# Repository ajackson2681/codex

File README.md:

# Codex

The Codex is an attempt at an open-source, distraction-free writing device inspired somewhat by the AlphaSmart Neo (at least the display was). The Codex pairs a 40x4 character LCD with USB HID keyboard support, and SD card storage. For a more in-depth summary/breakdown, you can visit the page I have on my website: [Codex Web Page](https://adamjackson.dev/codex.html).

---

## Project Status

Codex is under active development. Current state:

**Working:**
- [x] LCD driver
  - Originally used a derivation of the Arduino LiquidCrystal library (noted below under [Libraries Used](#libraries-used) and [Acknowledgements](#acknowledgments)). I have since written a custom one from the ground up specific for this project.
- [x] USB HID keyboard input via TinyUSB
- [x] Gap buffer with insert/delete/backspace
- [x] Character, word, line, frame, and document navigation
- [x] Frame buffer rendering (LCD stays in sync with cursor position)
- [x] SD card read/write (FatFs via [no-OS-FatFS-SD-SPI-RPi-Pico](https://github.com/carlk3/no-OS-FatFS-SD-SPI-RPi-Pico))
- [x] Document save/load
- [x] File selection on boot
- [x] Tab handling (inserted as two spaces)
- [x] Home/End at line, frame, and document scope
- [x] Card detect

**In progress / planned:**
- [ ] Keyboard shortcut finalization
- [ ] Save new document/give file name
- [ ] PWM backlight brightness control (potentiometer on one of the analog pins + transistor)
- [ ] Rev 2+ PCB: LiPo + boost converter, switchable external/battery power input, finalized sockets for ribbon cables/harnesses
- [ ] Final Enclosure (currently a wedge shape)
- [ ] Documentation: build guide, BOM, update procedure, etc.

**Maybes**
- [ ] Ability to change file after startup

**Explicitly out of scope (for now):**
- Text selection / clipboard
- Undo/redo
- Rich text or formatting of any kind

---

## Hardware

### Bill of Materials (high level)

| Component | Notes |
|---|---|
| Raspberry Pi Pico (RP2040) | Mounted via socket currently, likely castellated edge pads on the final PCB |
| 40x4 ST7066U character LCD | Dual controller (EN1/EN2), 4-bit mode |
| USB OTG converter | USB port for keyboard |
| SD card socket | SPI mode |
| Slide potentiometers (x2) | Contrast (to LCD V0) and brightness (to analog GPIO) |
| BC547 NPN transistor | PWM backlight switching |
| TP61090 boost converter | LiPo → 5V (Rev 2+) |
| MCP73871 charge controller | LiPo charge circuit (Rev 2+) |
| L7805 linear regulator | Bench/external power path (Rev0-Rev2, won't be on Rev3) |
| SPDT switch | Selects external 5V vs. LiPo/boost power source (Rev2 only), acts as power switch (Rev0 & Rev1) |
| LiPo cell | (Rev 2+) |

### PCB Revisions

| Rev | Purpose | Status |
|---|---|---|
| **Breadboard** | Initial validation: LCD, USB host, SD card | Done | 
| **Rev 0** | First PCB, puts the breadboard on a dedicated PCB, adds a power switch, adds filtering capacitors | Done |
| **Rev 1** | Fixes mistakes from Rev0. Sill uses socketed footprints for SD card and Pico. Adds breakout pins for contrast/brightness potentiometers, adds PWM backlight transistor. | Validating |
| **Rev 2** | Dedicated SD card slot, finalized sockets for IDC, potentiometers, and LED power. Pico footprint will allow sockets _or_ solder directly via castellated holes. 5v linear regulator will remain, with an optional switch for swapping to using a 5v direct power source (planned as a Powerboost 1000 module). | Designing |
| **Rev 3** | Removal of 5v linear regulator. Move to all SMD components for assembly by fab house. | Planned |
| **???** | Anything beyond Rev3 will only happen if I make dumb mistakes (and I probably will).

## Firmware

Built with the **Raspberry Pi Pico SDK**

### Libraries used

- Originally used a derivation of [LiquidCrystal440](https://github.com/jurs/liquidcrystal440), which is in turn a derivation of the [Original Arduino Library](https://github.com/arduino-libraries/LiquidCrystal).
  - Now uses a driver that is purpose-written for this device 
- **TinyUSB** - USB HID host
- **no-OS-FatFS-SD-SPI-RPi-Pico** - SD card / FAT filesystem (submodule)

### Recovery

If a firmware update fails or the device won't boot, hold **BOOTSEL** while connecting the Pico to a computer via USB. It will appear as a USB mass storage device. Then drag and drop a known-good `.uf2` to restore it. This is a hardware bootloader built into the RP2040 and cannot be bricked by firmware alone.

---

## Enclosure

Designed in FreeCAD. It has a sort of wedge factor with the 40x4 LCD forming most of the angled top face. Slide potentiometers for brightness and contrast are mounted on the front, with the the keyboard USB port and SD card slot to the right of those. FCStd files are located `3dmodels/` (I'm just committing the whole blob since I don't really know a better way to do it for freecad files in git).

---

## Keyboard Compatibility

The Codex _should_ work with any standard USB HID keyboard, both wired or via a wireless USB dongle. The Codex does **not** support bluetooth keyboards.

### Recommended

For a compact keyboard, a 65% or 75% layout is recommended for dedicated Home/End/Page Up/Page Down/Arrow keys without needing Fn combinations. Otherwise, pretty much whatever you're most comfortable with. I use an Epomaker TH80SE, which is a 75% keyboard. However, that doesn't have a dedicated "End" key (it's FN+PgDown). Something like the [Epomaker x Aula F65](https://epomaker.com/products/epomaker-aula-f65) or [Epomaker x Aula F75](https://epomaker.com/products/epomaker-aula-f75) could maybe be good choices that include all the buttons.

---

## Keyboard Shortcuts (WIP)

| Shortcut | Primary Action | Secondary Action
|---|---|---|
| Arrow keys | Move cursor (character / line) | |
| Ctrl + ←/→ | Move by word | |
| Ctrl + ↑/↓ | Jump to start/end of frame | Shift view by one full frame if at frame boundaries |
| Page Up/Page Down | Shift view by one full frame | |
| Home / End | Start/end of current line | |
| Ctrl + Home/End | Jump to start/end of current frame | |
| Ctrl + Shift + Home/End | Jump to start/end of document | |
| Tab | Insert two spaces | |
| Ctrl + S | Save current document to SD card | |
| Ctrl + Shift + I | Open document info (filename, size, etc) | |

---

## License

The Codex uses a split-license approach:

- All non-third-party code: **GPL v3**
- Hardware (`pcb/`) and Enclosures (`3dmodels/`): **CERN-OHL-S v2**

All third-party libraries retain their original licensing:

- TinyUSB: **MIT**
- no-OS-FatFS-SD-SPI-RPi-Pico **Apache 2.0**

See the `LICENSE` file in each directory for full text.

---

## Acknowledgments

- [LiquidCrystal](https://github.com/arduino-libraries/LiquidCrystal) original LCD library for Arduino, modified by jurs to support 40x4 displays
- [LiquidCrystal440](https://github.com/jurs/liquidcrystal440) modification of the original LiquidCrystal library by jurs, and that this project uses with small modifications.
- [no-OS-FatFS-SD-SPI-RPi-Pico](https://github.com/carlk3/no-OS-FatFS-SD-SPI-RPi-Pico)
  by carlk3
- [TinyUSB](https://github.com/hathach/tinyusb) USB HID stack
- The AlphaSmart Neo, for the original inspiration (sort of)
- The [r/writerdeck](https://reddit.com/r/writerdeck) community

---

## Contributing

The Codex is a work in progress and a personal project, but issues, ideas, and pull requests are welcome. If you build one, I'd love to hear about it.

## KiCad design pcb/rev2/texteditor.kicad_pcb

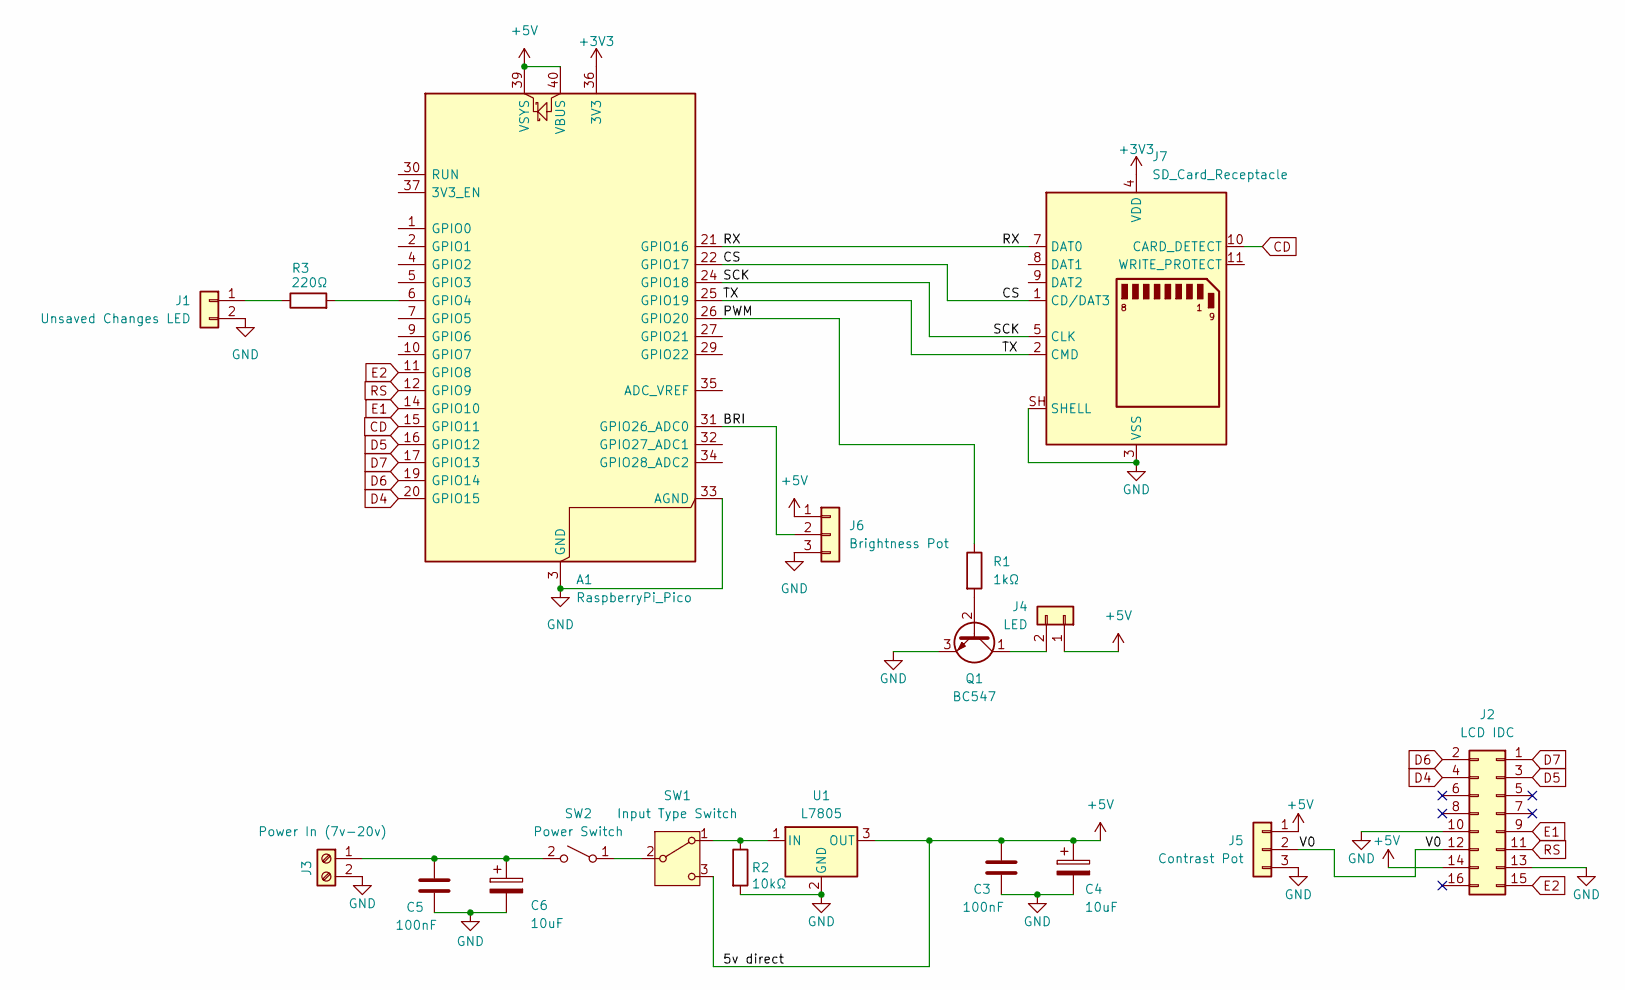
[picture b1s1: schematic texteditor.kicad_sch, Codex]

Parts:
A1: RaspberryPi_Pico; RaspberryPi_Pico_Common_Unspecified
C3, C5: 100nF; C_Disc_D4.7mm_W2.5mm_P5.00mm
C4, C6: 10uF; C_Radial_D4.0mm_H5.0mm_P1.50mm
J1: Unsaved Changes LED; JST_XA_B02B-XASK-1_1x02_P2.50mm_Vertical
J2: LCD IDC; IDC-Header_2x08_P2.54mm_Vertical
J3: Power In (7v-20v); TerminalBlock_Phoenix_PT-1,5-2-5.0-H_1x02_P5.00mm_Horizontal
J4: LED; JST_XA_B02B-XASK-1_1x02_P2.50mm_Vertical
J5: Contrast Pot; JST_XA_B03B-XASK-1_1x03_P2.50mm_Vertical
J6: Brightness Pot; JST_XA_B03B-XASK-1_1x03_P2.50mm_Vertical
J7: SD_Card_Receptacle; 693063010911
Q1: BC547; TO-92_Inline
R1: 1kΩ; R_Axial_DIN0207_L6.3mm_D2.5mm_P10.16mm_Horizontal
R2: 10kΩ; R_Axial_DIN0207_L6.3mm_D2.5mm_P10.16mm_Horizontal
R3: 220Ω; R_Axial_DIN0207_L6.3mm_D2.5mm_P10.16mm_Horizontal
SW1: Input Type Switch; PinHeader_1x03_P2.54mm_Vertical
SW2: Power Switch; JST_XA_B02B-XASK-1_1x02_P2.50mm_Vertical
U1: L7805; PinSocket_1x03_P2.54mm_Vertical

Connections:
+3V3: A1.36 (3V3), J7.4 (VDD)
+5V: A1.39 (VSYS), A1.40 (VBUS), C3.1, C4.1, J2.14, J4.1, J5.1, J6.1, SW1.3 (C), U1.3 (OUT)
/BRI: A1.31 (GPIO26_ADC0), J6.2
/CS: A1.22 (GPIO17), J7.1 (CD/DAT3)
/PWM: A1.26 (GPIO20), R1.1
/RX: A1.21 (GPIO16), J7.7 (DAT0)
/SCK: A1.24 (GPIO18), J7.5 (CLK)
/TX: A1.25 (GPIO19), J7.2 (CMD)
/V0: J2.12, J5.2
CD: A1.15 (GPIO11), J7.10 (CARD_DETECT)
D4: A1.20 (GPIO15), J2.4
D5: A1.16 (GPIO12), J2.3
D6: A1.19 (GPIO14), J2.2
D7: A1.17 (GPIO13), J2.1
E1: A1.14 (GPIO10), J2.9
E2: A1.11 (GPIO8), J2.15
GND: A1.3 (GND), A1.8 (GND), A1.13 (GND), A1.18 (GND), A1.23 (GND), A1.28 (GND), A1.33 (AGND), A1.38 (GND), C3.2, C4.2, C5.2, C6.2, J1.2, J2.10, J2.13, J3.2, J5.3, J6.3, J7.3 (VSS), J7.6 (VSS), J7.SH (SHELL), Q1.3 (E), R2.2, U1.2 (GND)
unnamed: A1.6 (GPIO4), R3.2
unnamed: J1.1, R3.1
unnamed: C5.1, C6.1, J3.1, SW2.2 (B)
unnamed: J4.2, Q1.1 (C)
unnamed: Q1.2 (B), R1.2
unnamed: R2.1, SW1.1 (A), U1.1 (IN)
unnamed: SW1.2 (B), SW2.1 (A)
RS: A1.12 (GPIO9), J2.11

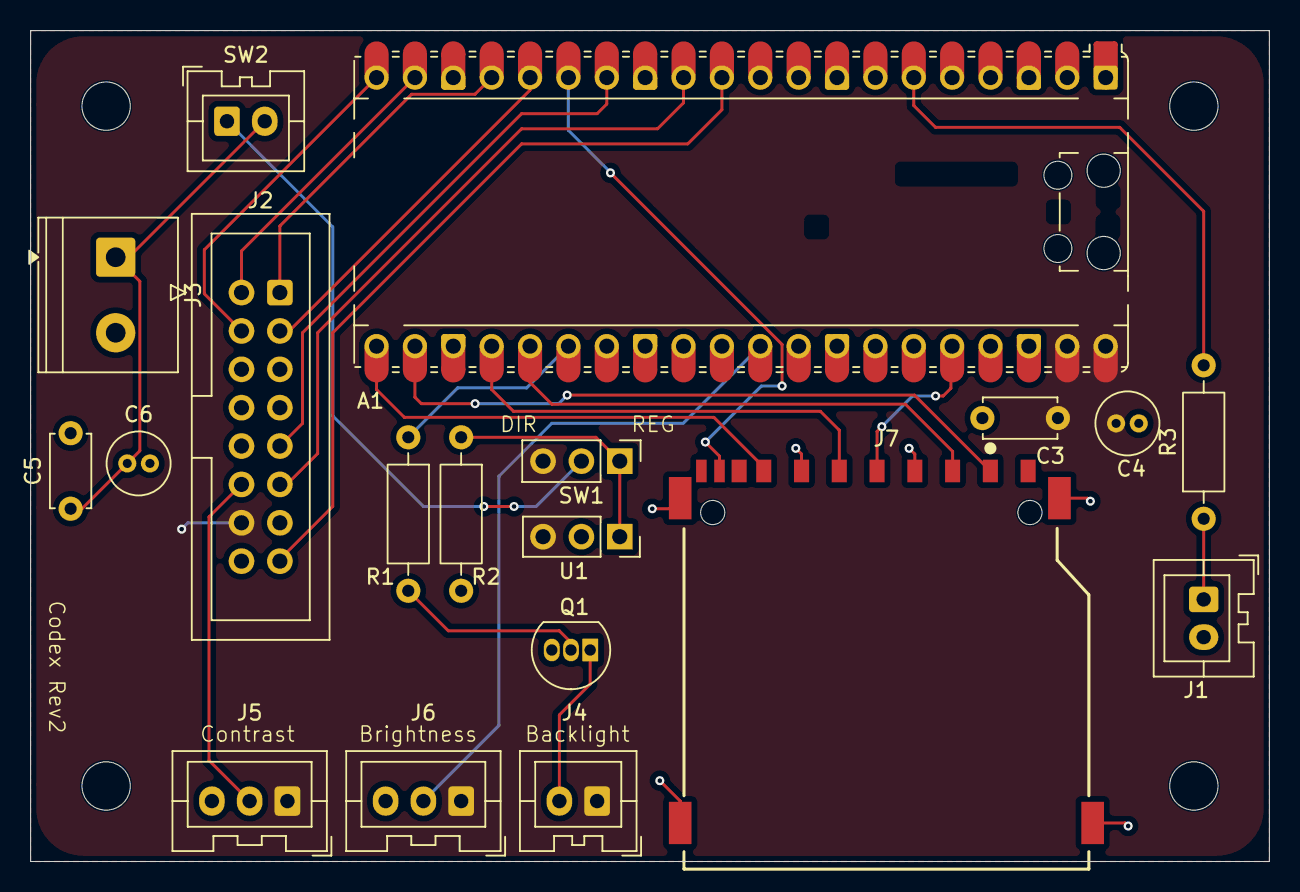
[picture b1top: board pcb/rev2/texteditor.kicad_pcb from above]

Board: 2 copper layers, 82.0 x 55.0 mm, 19 parts (0 on the bottom side), 25 nets.

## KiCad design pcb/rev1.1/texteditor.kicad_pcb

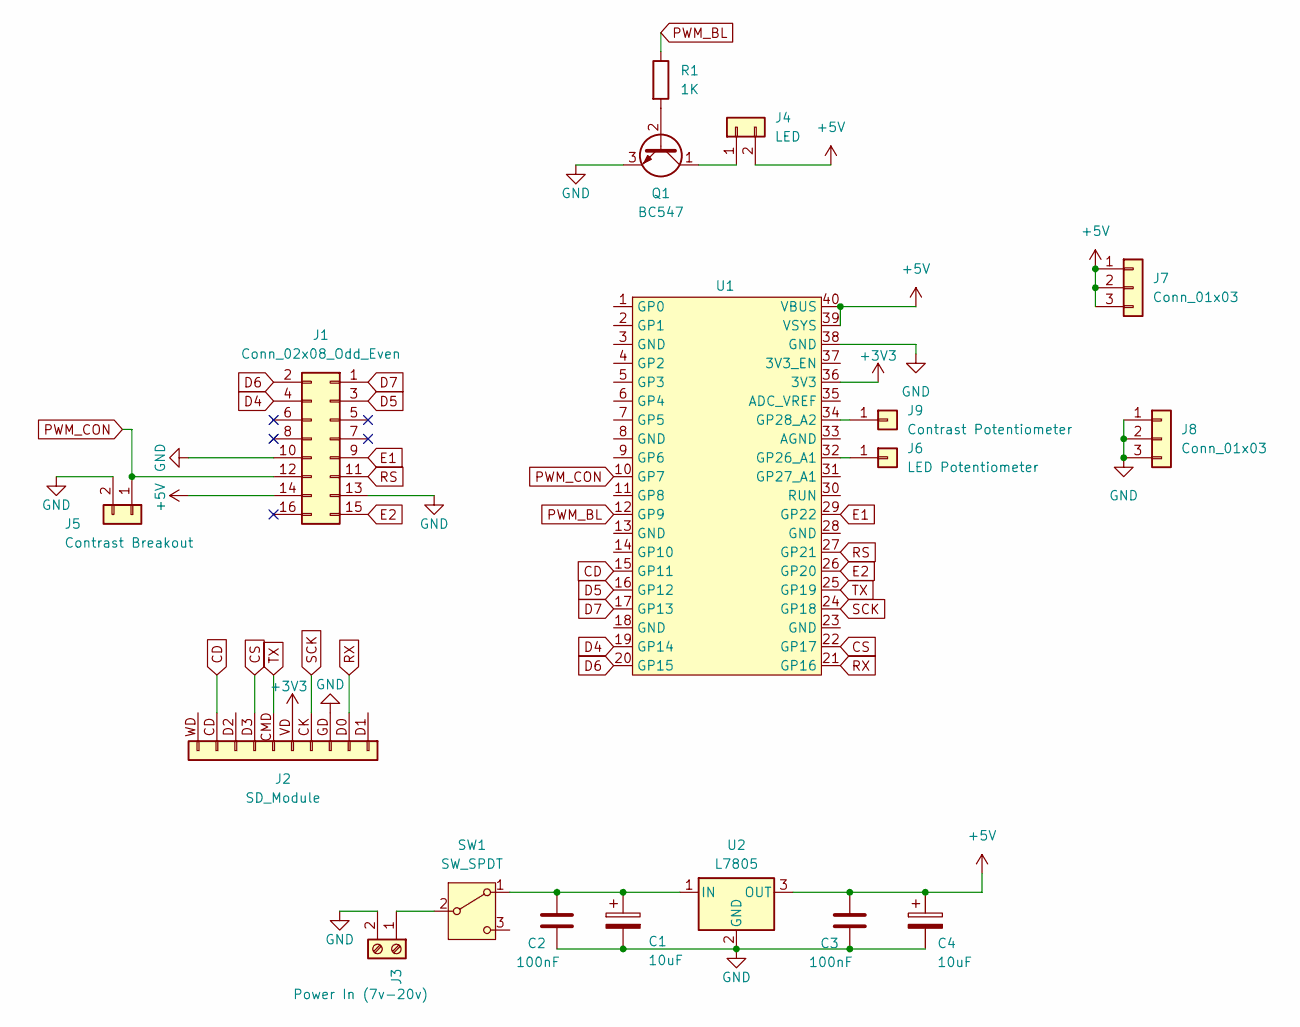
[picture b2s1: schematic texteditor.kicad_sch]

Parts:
C1, C4: 10uF; C_Radial_D4.0mm_H5.0mm_P1.50mm
C2, C3: 100nF; C_Disc_D4.7mm_W2.5mm_P5.00mm
J1: Conn_02x08_Odd_Even; pico_idc_connector
J2: SD_Module
J3: Power In (7v-20v); TerminalBlock_Phoenix_MKDS-1,5-2-5.08_1x02_P5.08mm_Horizont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
J4: LED; PinSocket_1x02_P2.54mm_Vertical
J5: Contrast Breakout; PinSocket_1x02_P2.54mm_Vertical
J6: LED Potentiometer; PinHeader_1x01_P2.54mm_Vertical
J7, J8: Conn_01x03; PinHeader_1x03_P2.54mm_Vertical
J9: Contrast Potentiometer; PinHeader_1x01_P2.54mm_Vertical
Q1: BC547; TO-92_Inline
R1: 1K; R_Axial_DIN0204_L3.6mm_D1.6mm_P7.62mm_Horizontal
SW1: SW_SPDT; PinHeader_1x03_P2.54mm_Vertical
U1: pico_2x20
U2: L7805; PinSocket_1x03_P2.54mm_Vertical

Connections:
+5V: C3.1, C4.1, J1.14, J4.2, J7.1, J7.2, J7.3, U1.39 (VSYS), U1.40 (VBUS), U2.3 (OUT)
CD: J2.CD (Pin_9), U1.15 (GP11)
CS: J2.D3 (Pin_7), U1.22 (GP17)
D4: J1.4, U1.19 (GP14)
D5: J1.3, U1.16 (GP12)
D6: J1.2, U1.20 (GP15)
D7: J1.1, U1.17 (GP13)
E1: J1.9, U1.29 (GP22)
E2: J1.15, U1.26 (GP20)
GND: C1.2, C2.2, C3.2, C4.2, J1.10, J1.13, J2.GD (Pin_3), J3.2, J5.2, J8.1, J8.2, J8.3, J9.3, Q1.3 (E), U1.38 (GND), U2.2 (GND); also elsewhere on the board
unnamed: J3.1, SW1.2 (B)
unnamed: J4.1, Q1.1 (C)
unnamed 12: J6.1, U1.32 (GP26_A1); also elsewhere on the board
unnamed: Q1.2 (B), R1.2
unnamed: C1.1, C2.1, SW1.1 (A), U2.1 (IN)
PWM_BL: R1.1, U1.12 (GP9)
PWM_CON: J1.12, J5.1, U1.10 (GP7)
RS: J1.11, U1.27 (GP21)
RX: J2.D0 (Pin_2), U1.21 (GP16)
SCK: J2.CK (Pin_4), U1.24 (GP18)
TX: J2.CMD (Pin_6), U1.25 (GP19)

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
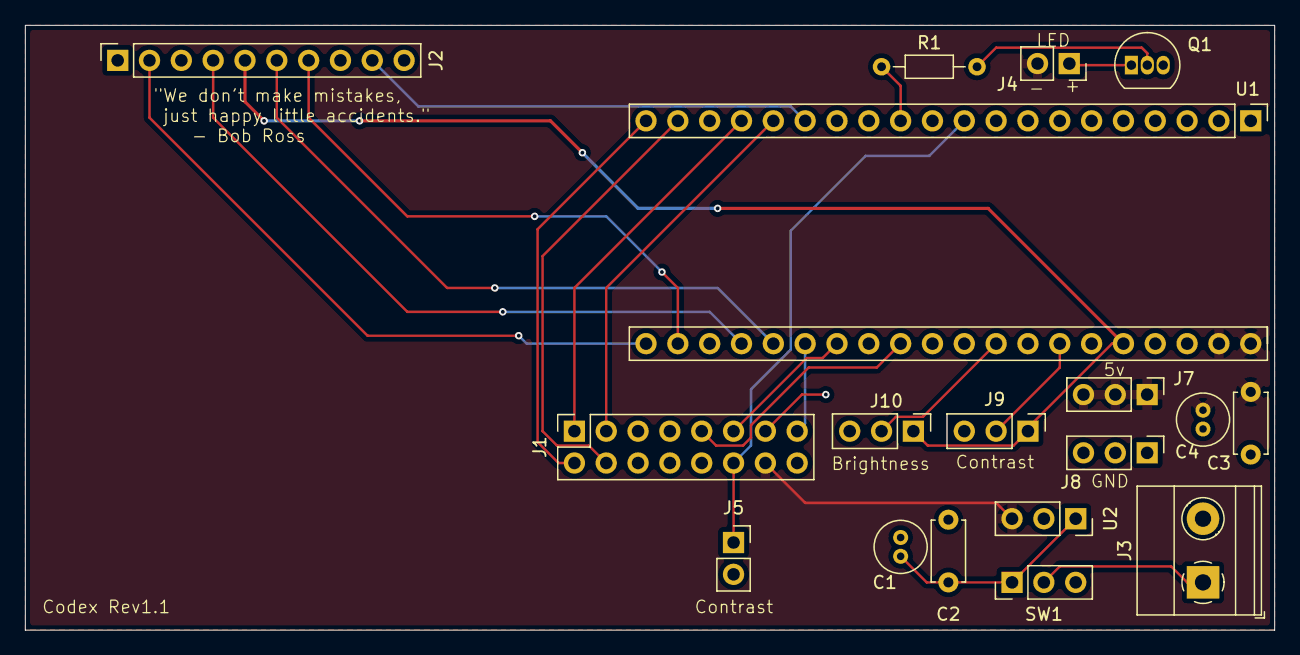
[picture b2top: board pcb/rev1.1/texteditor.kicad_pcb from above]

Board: 2 copper layers, 99.7 x 48.3 mm, 18 parts (0 on the bottom side), 23 nets.

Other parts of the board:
J10: Brightness Pot; PinHeader_1x03_P2.54mm_Vertical

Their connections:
GND: J10.3; also elsewhere on the board
unnamed 12: J10.2; also elsewhere on the board

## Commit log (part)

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2026-04-03 Initial code commit
    LCD initialization works and keyboard input does too.
    Everything else still in progress
2026-04-16 Commit fatfs submodule
    Includes a really basic example of writing
2026-04-16 commit stuff I missed?
2026-04-16 Update CMakeLists to use project root for fatfs submodule
2026-05-17 Basic text navigation working
    Need to finish advanced text editing
    Saving/Loading to SD card
2026-05-17 Upload rev0 schematic and design files
2026-05-18 New board spin
    - Fixes E1 pin misrouted to ground
    - Rotates SD module socket so that it sits above the board correctly
    - Breaks out LCD v0 for contrast adjust
    - Adds a transistor for PWM control of LED backlight
    - Moves power switch to between power input and regulator, rather than after. Prevents the regulator from draining any attached battery when power is off
    - Adds additional 5v and GND test points
2026-05-23 Better text naviagtion
    Also just a ton of QOL improvements, including moving keyboard processing to its own class, creating a config header for specifying the pinout of the LCD, adding an LCD string write function, a globa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
2026-05-27 Add tab insert, Fix f_open
2026-06-05 Add filesystem utility class and create a Globals.cpp file
2026-06-07 rev0.1 -> rev1 pcb
    Finalized design since I sent it in for fabrication
2026-06-07 More text navigation complete, and added better state management
2026-06-08 Basic document selection working
    I still need to get the ability to create a new document, name it, and then load into it. I also need to figure out how to go BACK to document selection if the user wants to switch their document wit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
2026-06-11 Upload codex freecad model
2026-06-11 update gitignore
2026-06-16 Update gitignore, add additional license files, and add a readme
2026-06-18 Add version number and helper function
2026-06-20 Use better version string filling
    Idk what I was thinking
2026-06-20 WIP lcd driver
2026-06-20 Remove old LiquidCrystal driver
2026-06-20 General cleanup
2026-06-20 Update some comments
2026-06-20 Fix after rebase
2026-06-20 Cursor should follow the position correctly now (I think)
2026-06-20 Combine redundant methods
    sendChar and sendCommand did essentially the same thing, just set the RS pin differently. This just combines them into one method called "sendByte" which takes a bool in the parameters for specifying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
    It also makes the delay be a default parameter, so we only need to supply that if we want a different delay than the default 40 us
2026-06-20 Use new LCD driver in main program
2026-06-20 Fix weird lines 3 & 4 error with the LCD
2026-06-20 Remove LiquidCrystal license
    No longer using the library
2026-06-21 Add a script for removing all build artifacts
2026-06-21 Pass alt modifier to keyboard processor
    Might end up needing it for later key combos
2026-06-21 Better filesystem loading and file selection
    Uses callbacks and whatnot instead of weird indexing math in the texteditor.cpp file
    Also changes all static methods to use PascalCase
2026-06-21 Convert utility classes to namespaces
2026-06-21 code cleanup
2026-06-21 Implement new line insert above or below
2026-06-21 Add board rev-specific defines
2026-06-21 Fix file selection
    Also update version number and fix board defines
    technically, rev0 didn't have a CD pin, but I wired it to GPIO 26 on my board. Rev1 offiically used GPIO 11
2026-06-21 have default document name for new docs
2026-06-21 Update readme again
2026-06-22 commit datasheet ref
2026-06-22 Should fix the weird flickering when writing
    Unfortunately there's a new bug where on the main screen the cursor goes back up to line 2 when it should be on line 3
2026-06-22 Use local references when inserting characters
    Direcly modifying the row and column did some weird stuff
2026-06-25 Better state management (in my opinion)
2026-06-25 remove step files from gitignore, and commit them
2026-06-25 Add pcb for custom pot module
2026-06-25 Add USB daughter board
    I figured with the front panel being ~ 5mm thick, that I'm not going to find a suitable passthrough cable, so this daughter board uses a vertical USB-A cable to expose the USB port from the pico
2026-06-25 Rotate footprints so that the micro usb is on the bottom realtive to how the board should be oriented
2026-06-27 Tweak pot module
2026-06-27 update fab outputs
2026-06-27 update usb fab outputs
